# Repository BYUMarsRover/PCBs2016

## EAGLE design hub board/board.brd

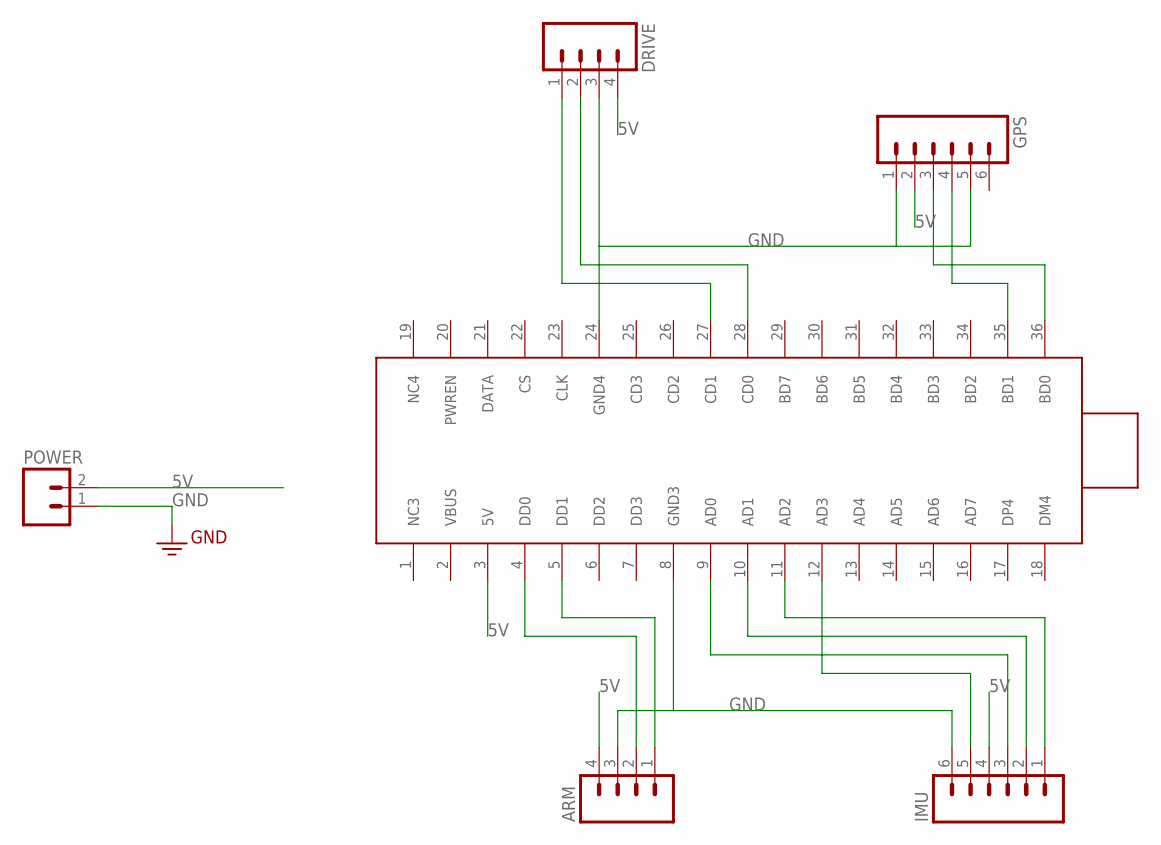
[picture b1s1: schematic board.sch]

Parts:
ARM: M04PTH; 1X04
DRIVE: M04PTH; 1X04
GPS: M06SILK_FEMALE_PTH; 1X06
IMU: M06SILK_FEMALE_PTH; 1X06
POWER: M02PTH; 1X02
U$1: HUB

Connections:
5V: ARM.4, DRIVE.4, GPS.2, IMU.4, POWER.2, U$1.3 (5V)
GND: ARM.3, DRIVE.3, GPS.1, GPS.5, IMU.6, POWER.1, U$1.8 (GND3), U$1.24 (GND4)
unnamed: ARM.2, U$1.4 (DD0)
unnamed: ARM.1, U$1.5 (DD1)
unnamed: DRIVE.2, U$1.28 (CD0)
unnamed: DRIVE.1, U$1.27 (CD1)
unnamed: IMU.3, U$1.9 (AD0)
unnamed: IMU.2, U$1.10 (AD1)
unnamed: IMU.5, U$1.12 (AD3)
unnamed: IMU.1, U$1.11 (AD2)
unnamed: GPS.3, U$1.36 (BD0)
unnamed: GPS.4, U$1.35 (BD1)

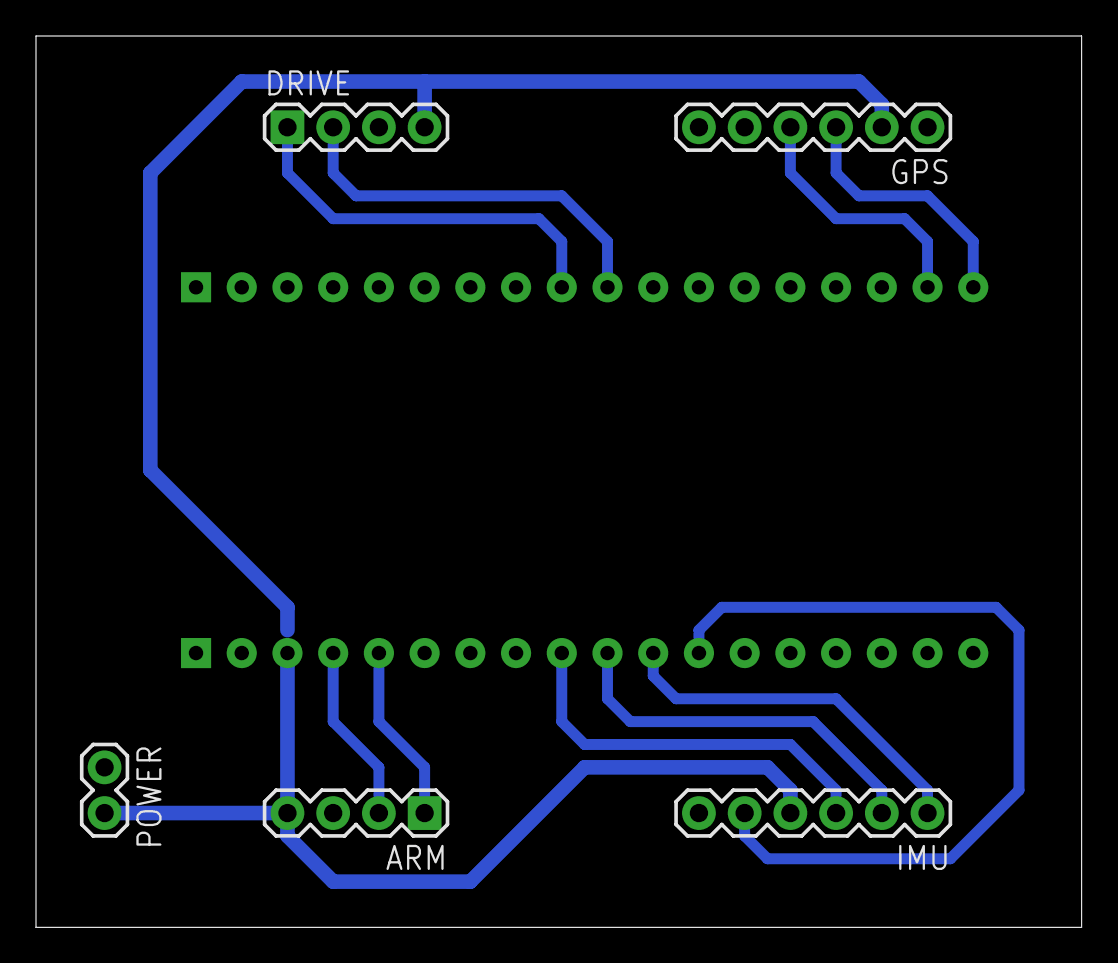
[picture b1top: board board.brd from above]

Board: 2 copper layers, 58.1 x 49.5 mm, 6 parts (1 on the bottom side), 12 nets.

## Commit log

2015-11-20 added hub board and library
2015-11-20 changed a directory name and added the .pro file

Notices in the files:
parts and their libraries:
SparkFun-Connectors: Licensing: Creative Commons ShareAlike 4.0 International - https://creativecommons.org/licenses/by-sa/4.0
